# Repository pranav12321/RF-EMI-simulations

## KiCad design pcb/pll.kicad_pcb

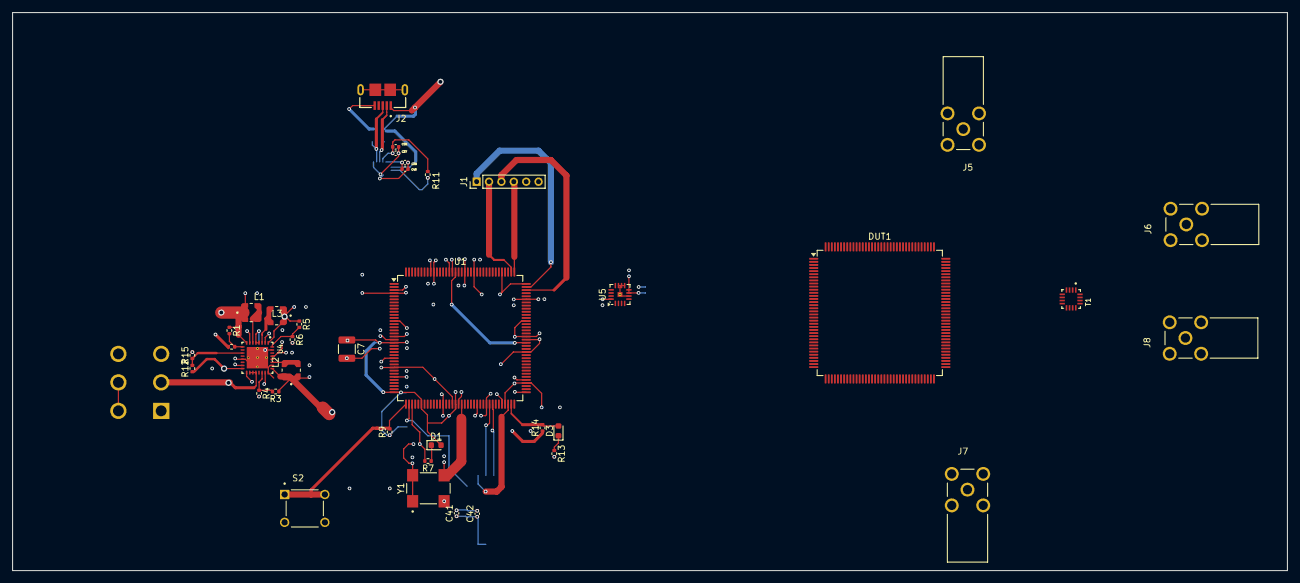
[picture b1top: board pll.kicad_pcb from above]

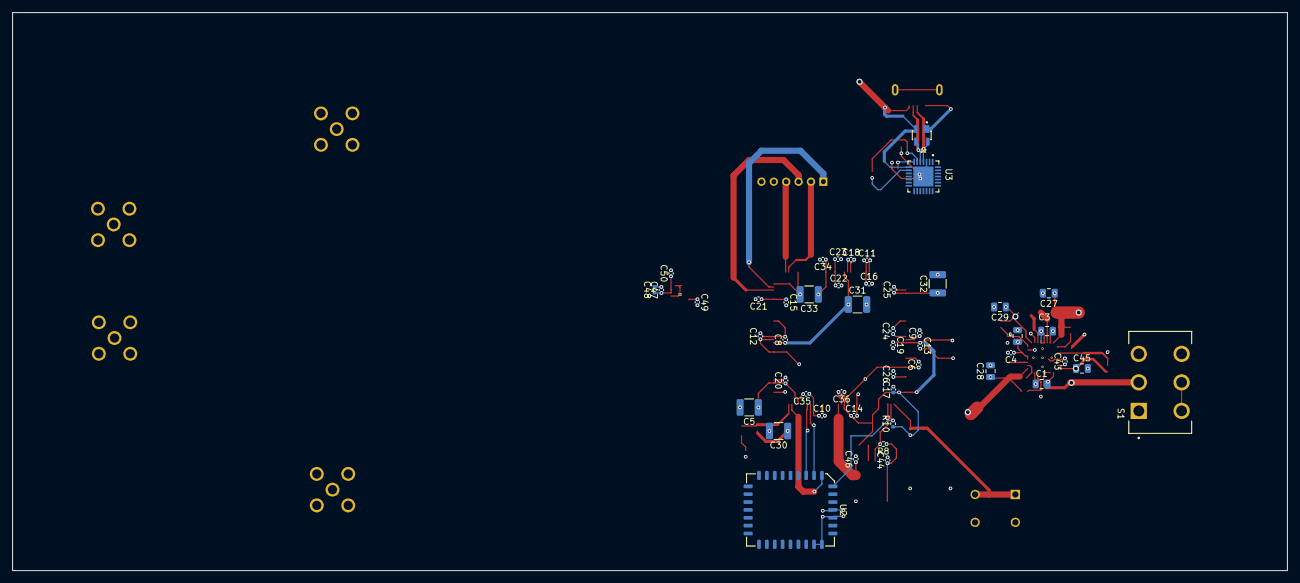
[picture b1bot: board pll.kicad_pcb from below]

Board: 4 copper layers, 205.8 x 90.1 mm, 87 parts (49 on the bottom side), 33 nets.

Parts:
C1, C2, C3: 10uF; C_0805_2012Metric
C4, C43: 1uF; C_0402_1005Metric
C5, C7, C30, C31, C32, C33: 100uF; C_1210_3225Metric
C6, C9, C10, C11, C12, C13, C14, C15, C16, C18, C21, C24, C34, C38, C39, C42: 4.7uF; C_0402_1005Metric
C8, C17, C19, C20, C22, C23, C25, C26, C35, C36: 0.47uF; C_0402_1005Metric
C27, C28, C29: 22uF; C_0805_2012Metric
C37, C40, C41, C44, C47, C48, C49, C50: 0.1uF; C_0402_1005Metric
C45: 2.2uF; C_0805_2012Metric
C46: 15pF; C_0402_1005Metric
D1, D3: LED; LED_0603_1608Metric
D2: SP0503BAHTG; SOT143
DUT1: TQFP-144_20x20mm_P0.5mm
J1: 6pin_2mm_jtag; 6p
J2: USB3090-XX-X_REVE2; GCT_USB3090-XX-X_REVE2
J5, J6, J7, J8: 85_SMA-50-0-144_111_YE; HUBER_SUHNER_85_SMA-50-0-144_111_YE
L1, L2, L3: L; IND_LPS3015-222MRC
R1, R2, R3, R4, R5, R6, R11: R; R_0402_1005Metric
R7, R13, R14: 330; R_0402_1005Metric
R8, R9, R10: 4.7K; R_0402_1005Metric
R12: 330k; R_0402_1005Metric
R15: 130k; R_0402_1005Metric
S1: GF-126-0159; SW_GF-126-0159
S2: TS02-66-43-BK-100-LCR-D; SW_TS02-66-43-BK-100-LCR-D
T1: QFN50P300X300X80-16N
U1: XC6SLX4-TQG144; TQFP-144_20x20mm_P0.5mm
U2: AT45DB161-JC; PLCC-32_11.4x14.0mm_P1.27mm
U3: CP2102N-A01-GQFN28; QFN50P500X500X80-29N
U4: TPS650250RHBR; IC_ADS125H01IRHBT
U5: DAC80504; Texas_RTE0016D_WQFN-16-1EP_3x3mm_P0.5mm_EP0.8x0.8mm_Thermal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
Y1: DSC1004AL1-001.0000; OSC_DSC1004AL1-001.0000

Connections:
/DACAnalogswitch/VDD: C37.1, C38.1, C45.1, C47.1, C48.1, C49.1, C50.1, R11.1, R12.1, U3.6 (VDD), U4.16 (VLDO1), U5.7 (VDD), U5.8 (GAIN), U5.16 (VIO)
/fpga/CSO_B: R10.2, U1.38 (IO_L65N_CSO_B_2), U2.4 (~CS)
/fpga/DONE: D3.2 (A), R14.2, U1.71 (DONE_2)
/fpga/EXT_CLOCK: C46.1, U1.55 (IO_L30N_GCLK0_USERCCLK_2), Y1.3 (OUT)
/fpga/INIT_B: R7.2, R8.2, U1.39 (IO_L65P_INIT_B_2)
/fpga/MISO: U1.65 (IO_L3P_D0_DIN_MISO_MISO1_2), U2.7 (SO)
/fpga/MOSI: U1.64 (IO_L3N_MOSI_CSI_B_MISO0_2), U2.6 (SI)
/fpga/PROG_B: R9.2, S2.1, S2.2, U1.37 (PROGRAM_B_2)
/fpga/SPI_CLK: U1.70 (IO_L1P_CCLK_2), U2.5 (SCK)
/fpga/TCK: J1.4 (TCK), U1.109 (TCK)
/fpga/TDI: J1.2 (TDI), U1.110 (TDI)
/fpga/TDO: J1.3 (TDO), U1.106 (TDO)
/fpga/TMS: J1.1 (TMS), U1.107 (TMS)
/fpga/VCCAUX: C5.1, C7.1, C10.1, C11.1, C12.1, C13.1, C14.1, C15.1, C16.1, C17.1, C18.1, C19.1, C20.1, C21.1, C22.1, C23.1, C27.1, C30.1, C33.1, C34.1, C35.1, C36.1, C41.1, C42.1, C44.1, D1.2 (A), J1.6 (VDD), L1.1, R1.1, R8.1, R9.1, R10.1, R14.1, U1.20 (VCCAUX), U1.36 (VCCAUX), U1.42 (VCCO_2), U1.53 (VCCAUX), U1.63 (VCCO_2), U1.69 (IO_L1N_M0_CMPMISO_2), U1.76 (VCCO_1), U1.86 (VCCO_1), U1.90 (VCCAUX), U1.103 (VCCO_1), U1.122 (VCCO_0), U1.125 (VCCO_0), U1.129 (VCCAUX), U1.135 (VCCO_0), U2.28 (~RESET), U2.29 (~WP), U2.32 (VCC), U4.8 (VDCDC1), Y1.1 (~STANDBY), Y1.4 (VDD)
/fpga/VCCINT: C6.1, C8.1, C9.1, C28.1, C31.1, L2.1, R3.1, U1.19 (VCCINT), U1.28 (VCCINT), U1.52 (VCCINT), U1.89 (VCCINT), U1.128 (VCCINT), U4.25 (VDCDC2)
/fpga/VCCO_3: C24.1, C25.1, C26.1, C29.1, C32.1, L3.1, R5.1, U1.4 (VCCO_3), U1.18 (VCCO_3), U1.31 (VCCO_3), U4.1 (VDCDC3)
/power/D+: D2.4, J2.3 (D+), U3.4 (D+)
/power/D-: D2.3, J2.2 (D-), U3.5 (D-)
/power/DEFDCDC1: R1.2, R2.1, U4.9 (DEFDCDC1)
/power/DEFDCDC2: R3.2, R4.1, U4.22 (DEFDCDC2)
/power/DEFDCDC3: R5.2, R6.1, U4.32 (DEFDCDC3)
/power/FB_LDO1: R12.2, R15.1, U4.11 (FB_LDO1)
/power/L1: L1.2, U4.6 (L1)
/power/L2: L2.2, U4.27 (L2)
/power/L3: L3.2, U4.3 (L3)
/power/VBUS: D2.2, J2.1 (VBUS), S1.1, U3.8 (VBUS)
/power/VCC: C1.1, C2.1, C3.1, C4.1, C43.1, S1.2, U4.4 (VINDCDC3), U4.5 (VINDCDC1), U4.15 (VINLDO), U4.18 (EN_DCDC3), U4.19 (EN_DCDC2), U4.20 (EN_DCDC1), U4.23 (MODE), U4.28 (VINDCDC2), U4.29 (VCC)
/usb-serial/VREGIN: C39.1, C40.1, U3.7 (VREGIN)
GND: C1.2, C2.2, C3.2, C4.2, C5.2, C6.2, C7.2, C8.2, C9.2, C10.2, C11.2, C12.2, C13.2, C14.2, C15.2, C16.2, C17.2, C18.2, C19.2, C20.2, C21.2, C22.2, C23.2, C24.2, C25.2, C26.2, C27.2, C28.2, C29.2, C30.2, C31.2, C32.2, C33.2, C34.2, C35.2, C36.2, C37.2, C38.2, C39.2, C40.2, C41.2, C42.2, C43.2, C44.2, C45.2, C46.2, C47.2, C48.2, C49.2, C50.2, D2.1, J1.5 (GND), J2.5 (GND), R2.2, R4.2, R6.2, R13.2, R15.2, S1.4, S1.5, S2.3, S2.4, U1.3 (GND), U1.13 (GND), U1.25 (GND), U1.49 (GND), U1.54 (GND), U1.60 (IO_L13P_M1_2), U1.68 (GND), U1.73 (SUSPEND), U1.77 (GND), U1.91 (GND), U1.96 (GND), U1.108 (GND), U1.113 (GND), U1.130 (GND), U1.136 (GND), U2.1 (GND), U3.3 (GND), U3.29 (GND), U4.2 (PGND3), U4.7 (PGND1), U4.13 (AGND2), U4.17 (EN_LDO), U4.24 (EN_VDD_ALIVE), U4.26 (PGND2), U4.31 (AGND1), U4.33 (EP), U5.6 (GND), U5.9 (RSTSEL), U5.10 (REFDIV), U5.11 (~LDAC), U5.17 (EP), Y1.2 (GND)
unnamed: D1.1 (K), R7.1
unnamed: D3.1 (K), R13.1
unnamed: R11.2, U3.9 (~RST)
SHIELD: J2.SH1 (SHIELD), J2.SH2 (SHIELD), J2.SH3 (SHIELD), J2.SH4 (SHIELD)

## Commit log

2025-10-16 test
2025-10-16 add modules femwell and openems
2026-01-09 fpga initial
2026-01-09 dut components update
2026-01-09 external crystal
2026-01-10 DAC/JTAG updates
2026-02-05 footprint/sch for amplifiers
2026-03-04 gitignore file
2026-03-04 ltspice sim for bias tee path
